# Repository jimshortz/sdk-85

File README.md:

This project contains assets for my Intel SDK-85 projects.

`.a80` files are assembled using `asm80` from
https://github.com/ogdenpm/c-ports. These can also be assembled using
the Intel ISIS `asm80` under Thames.

`.z80` files are assembled using `z80asm`
(https://github.com/AlbertVeli/z80asm) as installed by Homebrew.

The following sudirectories exist:
* simon - A clone of the 1978 Milton Bradley game.  Hand assembled!
* loader - A simple binary loader for 9600bps serial port
* chess - MicroChess by Peter Jennings and T O'Brien (1977)
* basic - Altair 8K BASIC by Microsoft (1978 version)

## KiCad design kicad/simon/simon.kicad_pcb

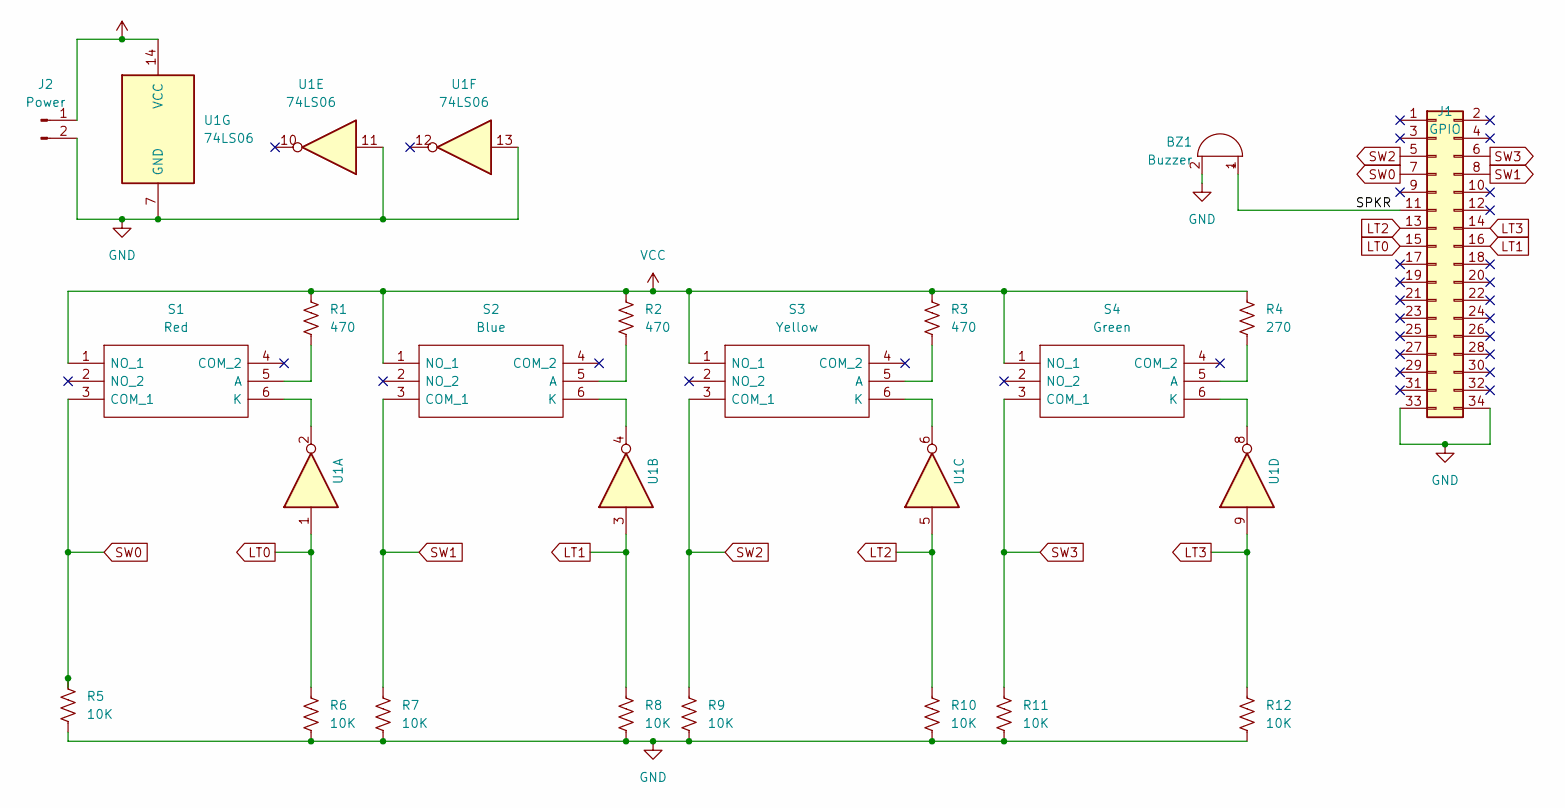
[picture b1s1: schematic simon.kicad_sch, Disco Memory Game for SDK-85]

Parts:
BZ1: Buzzer; XDCR_AT-1438-TWT-R; Manufacturer_Part_Number AT-1438-TWT-R; Mouser Part Number 665-AT-1438TWTR
J1: GPIO; PinSocket_2x17_P2.54mm_Vertical; Mouser Part Number 571-15342067
J2: Power; PinHeader_1x02_P2.54mm_Vertical; Manufacturer_Part_Number 5-146282-2; Mouser Part Number 571-5-146282-2
R1, R2, R3: 470; R_Axial_DIN0207_L6.3mm_D2.5mm_P10.16mm_Horizontal; Manufacturer_Part_Number CFR16J470R; Mouser Part Number 279-CFR16J470R
R4: 270; R_Axial_DIN0207_L6.3mm_D2.5mm_P10.16mm_Horizontal; Manufacturer_Part_Number CFR16J270R; Mouser Part Number 279-CFR16J270R
R5, R6, R7, R8, R9, R10, R11, R12: 10K; R_Axial_DIN0207_L6.3mm_D2.5mm_P10.16mm_Horizontal; Manufacturer_Part_Number CFR16J10K; Mouser Part Number 279-CFR16J10K
S1: Red; B3W9002Y1Y; Manufacturer_Part_Number B3W-9002-Y1Y; Mouser Part Number 653-B3W-9002-Y1Y
S2: Blue; B3W9002Y1Y; Manufacturer_Part_Number B3W-9002-Y1Y; Mouser Part Number 653-B3W-9002-Y1Y
S3: Yellow; B3W9002Y1Y; Manufacturer_Part_Number B3W-9002-Y1Y; Mouser Part Number 653-B3W-9002-Y1Y
S4: Green; B3W9002Y1Y; Manufacturer_Part_Number B3W-9002-Y1Y; Mouser Part Number 653-B3W-9002-Y1Y
U1: 74LS06; DIP-14_W7.62mm; Manufacturer_Part_Number SN74LS06N; Mouser Part Number 595-SN74LS06N

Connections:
/SPKR: BZ1.1 (-), J1.11
GND: BZ1.2 (+), J1.33, J1.34, J2.2, R5.2, R6.2, R7.2, R8.2, R9.2, R10.2, R11.2, R12.2, U1.7 (GND), U1.11, U1.13
LT0: J1.15, R6.1, U1.1
LT1: J1.16, R8.1, U1.3
LT2: J1.13, R10.1, U1.5
LT3: J1.14, R12.1, U1.9
unnamed: R1.2, S1.5 (A)
unnamed: S1.6 (K), U1.2
unnamed: R2.2, S2.5 (A)
unnamed: S2.6 (K), U1.4
unnamed: R3.2, S3.5 (A)
unnamed: S3.6 (K), U1.6
unnamed: R4.2, S4.5 (A)
unnamed: S4.6 (K), U1.8
SW0: J1.7, R5.1, S1.3 (COM_1)
SW1: J1.8, R7.1, S2.3 (COM_1)
SW2: J1.5, R9.1, S3.3 (COM_1)
SW3: J1.6, R11.1, S4.3 (COM_1)
VCC: J2.1, R1.1, R2.1, R3.1, R4.1, S1.1 (NO_1), S2.1 (NO_1), S3.1 (NO_1), S4.1 (NO_1), U1.14 (VCC)

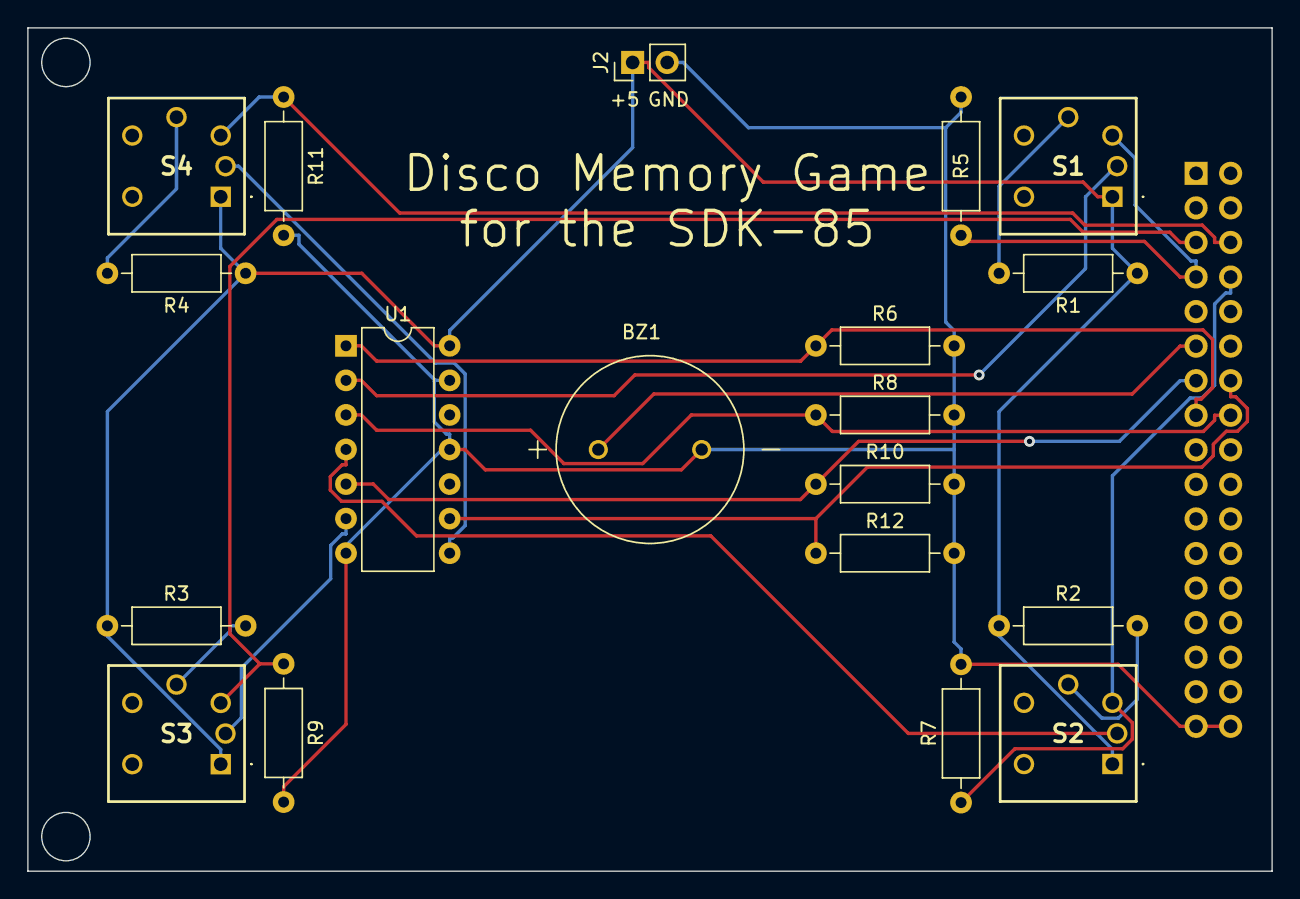
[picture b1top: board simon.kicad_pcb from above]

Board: 2 copper layers, 91.4 x 62.0 mm, 20 parts (1 on the bottom side), 19 nets.

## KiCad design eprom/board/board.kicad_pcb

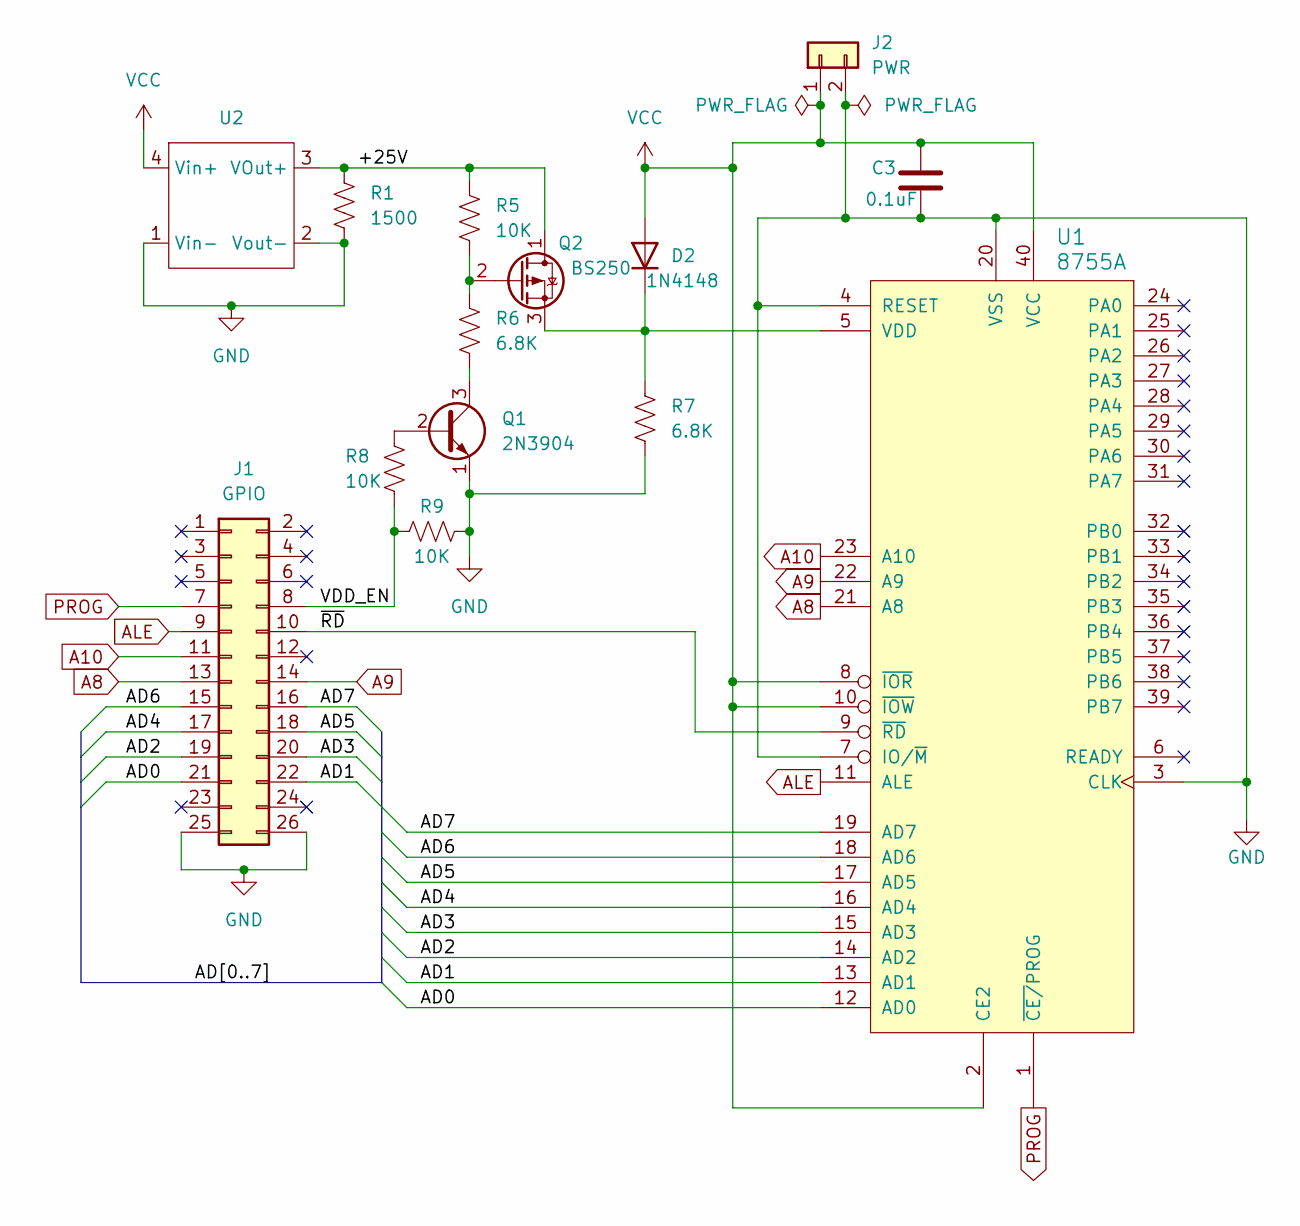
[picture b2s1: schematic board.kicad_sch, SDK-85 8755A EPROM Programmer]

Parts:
C3: 0.1uF; C_Disc_D9.0mm_W2.5mm_P5.00mm
D2: 1N4148; D_DO-41_SOD81_P7.62mm_Horizontal
J1: GPIO; PinHeader_2x13_P2.54mm_Vertical
J2: PWR; PinHeader_1x02_P2.54mm_Vertical
Q1: 2N3904; TO-92_Inline
Q2: BS250; TO-92_Inline
R1: 1500; R_Axial_DIN0207_L6.3mm_D2.5mm_P10.16mm_Horizontal
R5, R8, R9: 10K; R_Axial_DIN0207_L6.3mm_D2.5mm_P10.16mm_Horizontal
R6, R7: 6.8K; R_Axial_DIN0207_L6.3mm_D2.5mm_P10.16mm_Horizontal
U1: 8755A; 3M_Textool_240-1288-00-0602J_2x20_P2.54mm
U2: MT3608_Module

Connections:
/+25V: Q2.1 (D), R1.2, R5.2, U2.3 (VOut+)
/AD0: J1.21, U1.12 (AD0)
/AD1: J1.22, U1.13 (AD1)
/AD2: J1.19, U1.14 (AD2)
/AD3: J1.20, U1.15 (AD3)
/AD4: J1.17, U1.16 (AD4)
/AD5: J1.18, U1.17 (AD5)
/AD6: J1.15, U1.18 (AD6)
/AD7: J1.16, U1.19 (AD7)
/VDD_EN: J1.8, R8.1, R9.1
/~RD: J1.10, U1.9 (~RD)
A8: J1.13, U1.21 (A8)
A9: J1.14, U1.22 (A9)
A10: J1.11, U1.23 (A10)
ALE: J1.9, U1.11 (ALE)
GND: C3.2, J1.25, J1.26, J2.2, Q1.1 (E), R1.1, R7.1, R9.2, U1.3 (CLK), U1.4 (RESET), U1.7 (IO/~M), U1.20 (VSS), U2.1 (Vin-), U2.2 (Vout-)
unnamed: D2.1 (K), Q2.3 (S), R7.2, U1.5 (VDD)
unnamed: Q1.2 (B), R8.2
unnamed: Q1.3 (C), R6.1
unnamed: Q2.2 (G), R5.1, R6.2
PROG: J1.7, U1.1 (~CE/PROG)
VCC: C3.1, D2.2 (A), J2.1, U1.2 (CE2), U1.8 (~IOR), U1.10 (~IOW), U1.40 (VCC), U2.4 (Vin+)

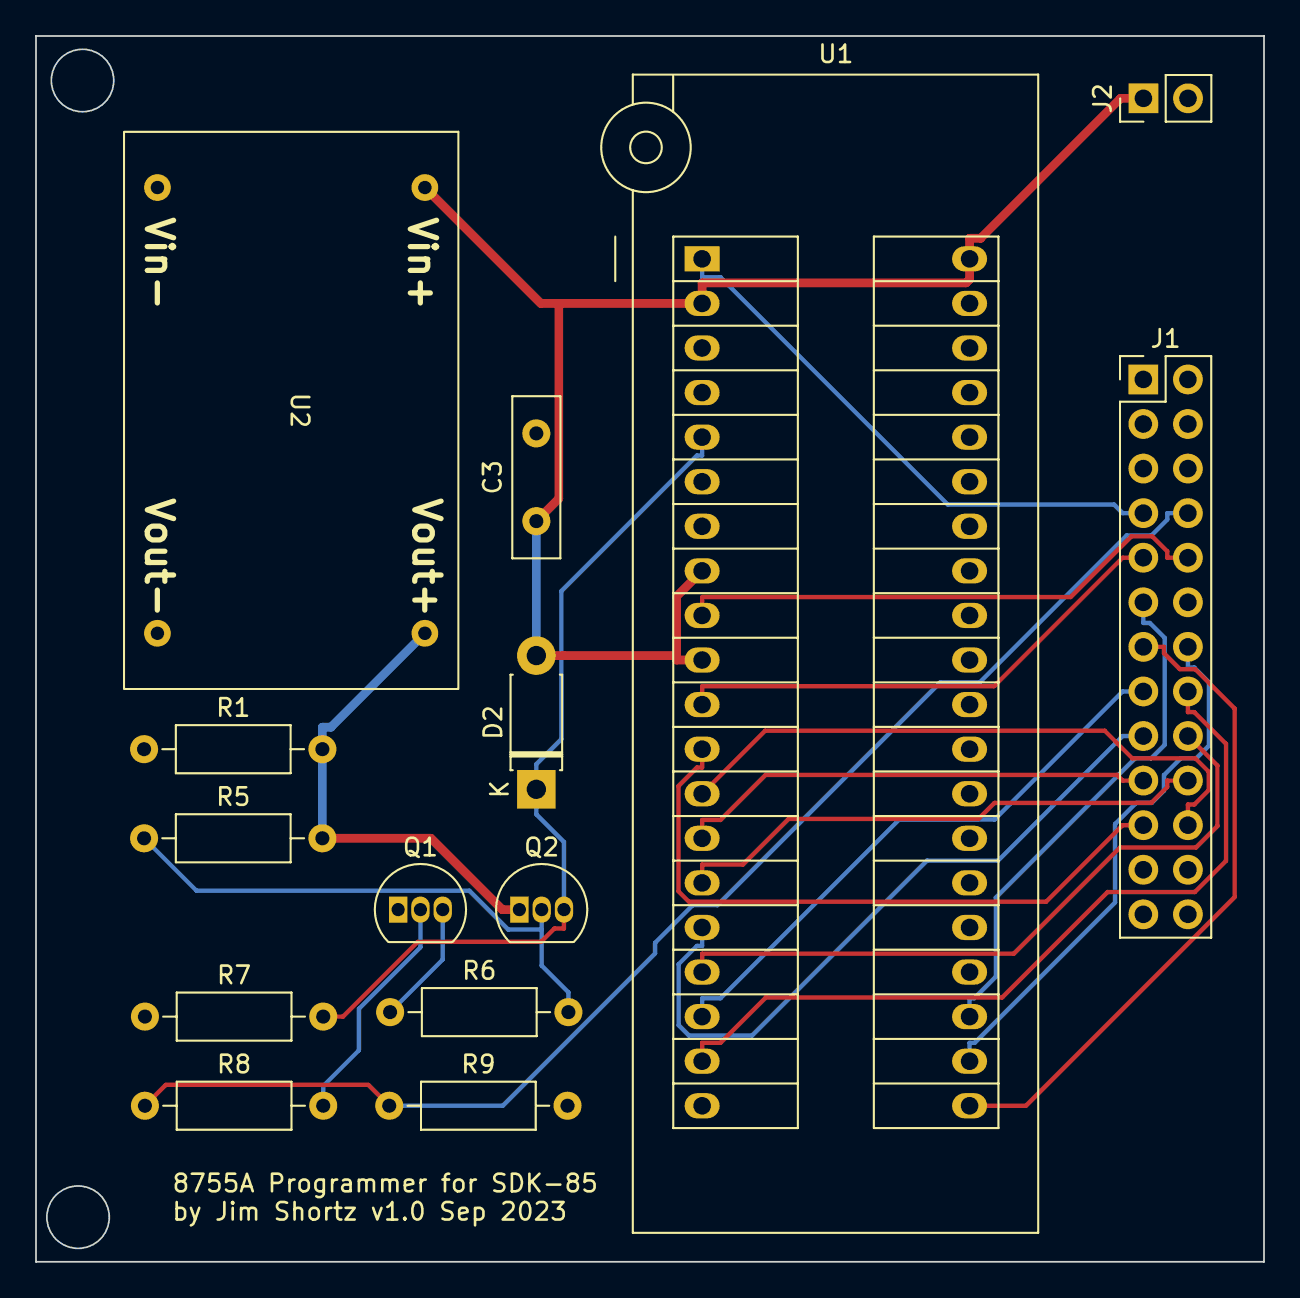
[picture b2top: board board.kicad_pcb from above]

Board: 2 copper layers, 70.0 x 69.8 mm, 14 parts (0 on the bottom side), 22 nets.

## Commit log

2023-08-10 Initial Simon and BASIC assets
2023-09-03 Simon - Added 250ms pause between player and computer's turn for better playability. Removed gaps and relocated to expansion RAM.
    Loader - Added simple binary checksum loader and correspond checksum
    calculation program.
    Chess - Added Microchess (Peter Jennings - 1977)
    BASIC - Added Altair 8K BASIC (Microsoft - 1978)
2023-09-03 Added original binary for ease of use
2023-09-07 Added PL/M prime generator
2023-09-07 Improved loader.
2023-09-07 Fixed serial bug.
2023-09-11 Implemented Intel hex loader in PL/M
2023-09-21 Added KiCad files
2023-09-23 Original version with homebrew circuit
2023-09-23 Production version
2023-09-27 Simon board
2023-10-04 First working EPROM routines.
2023-10-05 Working EPROM burn code.
2023-10-07 Added options to locate loader and hex loader to ROM.
2023-10-11 Added nice EPROM manager.
2023-10-14 Added dynamic command lookup. Changed ioinit to work if 8251 has already been setup.
2023-10-14 Changed hex loader to auto-start
2023-10-15 Rearraged utilities into sys/ directory. Standardized on hex files.
2023-10-15 Rearranged kicad files into single directory. Added primes comparison.
2023-10-15 Changed minloader default to load hexloader at f800
2023-10-15 Production version of Simon board.
2023-10-16 Fixed trace routing to speaker. This is the real production version.
2023-10-22 Updated to match PCB polarity.
2023-10-23 Updated board with larger holes, BOM, and part numbers. This corresponds to the community shared version (v1.0.1)
2023-10-23 Moved Simon to ROM.
2023-10-23 Patched to allow writes to 2800H.
2023-12-26 Added assembly language prime finder.
